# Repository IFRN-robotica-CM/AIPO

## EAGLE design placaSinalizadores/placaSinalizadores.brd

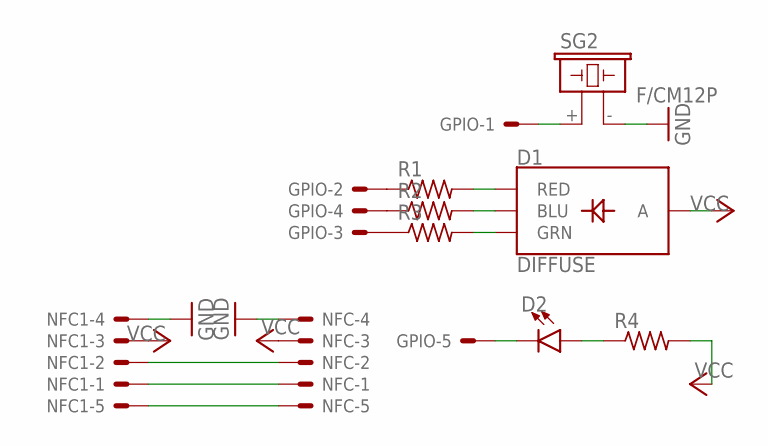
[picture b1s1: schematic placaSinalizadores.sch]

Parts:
D1: DIFFUSE; LED-RGB-THRU
D2: LED5MM; LED_5MM
GPIO: JST-XH-05-PIN-LONG-PAD; JST-XH-05-PACKAGE-LONG-PAD
NFC, NFC1: JST-XH-05-PIN-LONG-PAD; JST-XH-05-PACKAGE-LONG-PAD
R1, R2, R3, R4: R-US_0204/7; 0204/7
SG2: F/CM12P

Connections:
GND: NFC.4, NFC1.4, SG2.- (2)
unnamed: D1.1 (RED), R1.2
unnamed: D1.4 (BLU), R2.2
unnamed: D1.3 (GRN), R3.2
unnamed: D2.A, R4.1
unnamed: NFC.2, NFC1.2
unnamed: NFC.1, NFC1.1
unnamed: D2.K (C), GPIO.5
unnamed: GPIO.1, SG2.+ (1)
unnamed: GPIO.2, R1.1
unnamed: GPIO.4, R2.1
unnamed: GPIO.3, R3.1
unnamed: NFC.5, NFC1.5
VCC: D1.2 (A), NFC.3, NFC1.3, R4.2

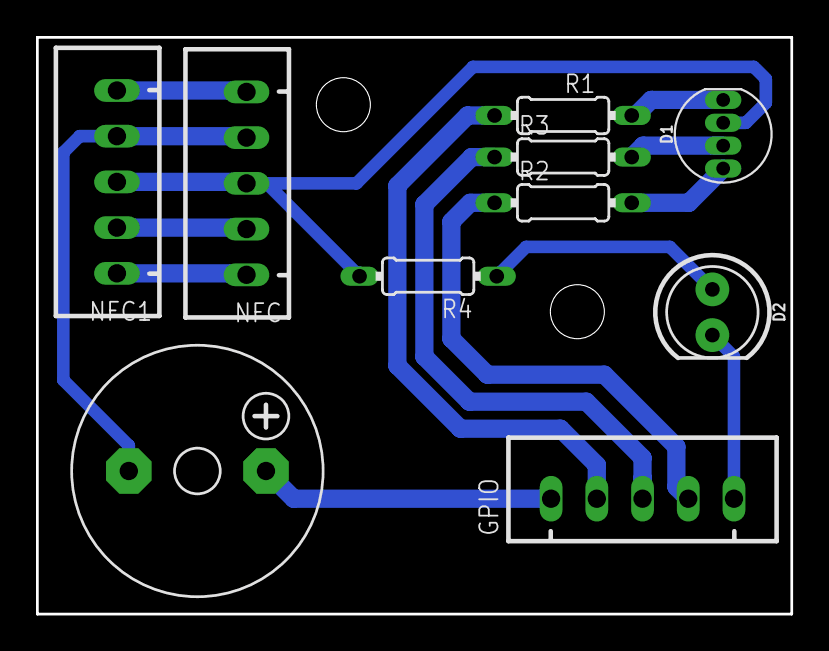
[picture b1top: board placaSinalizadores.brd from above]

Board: 2 copper layers, 41.9 x 32.0 mm, 10 parts (0 on the bottom side), 14 nets.

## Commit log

2024-06-11 CÓDIGO INICIAL
2024-06-11 Criação de classe para utilização do sensor RFID-RC522
2024-06-11 iniciando conexão com o broker
2024-08-14 arquivo top case PN532
2024-08-14 arquivos placa de sinalização
2024-08-14 top case com erros corrigidos
2024-09-15 placa de sinalização V2
    placa com conectores para o reset adicionados e correção do erro para o led rgb

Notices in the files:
parts and their libraries:
SparkFun-LED: Licensing: Creative Commons ShareAlike 4.0 International - https://creativecommons.org/licenses/by-sa/4.0
